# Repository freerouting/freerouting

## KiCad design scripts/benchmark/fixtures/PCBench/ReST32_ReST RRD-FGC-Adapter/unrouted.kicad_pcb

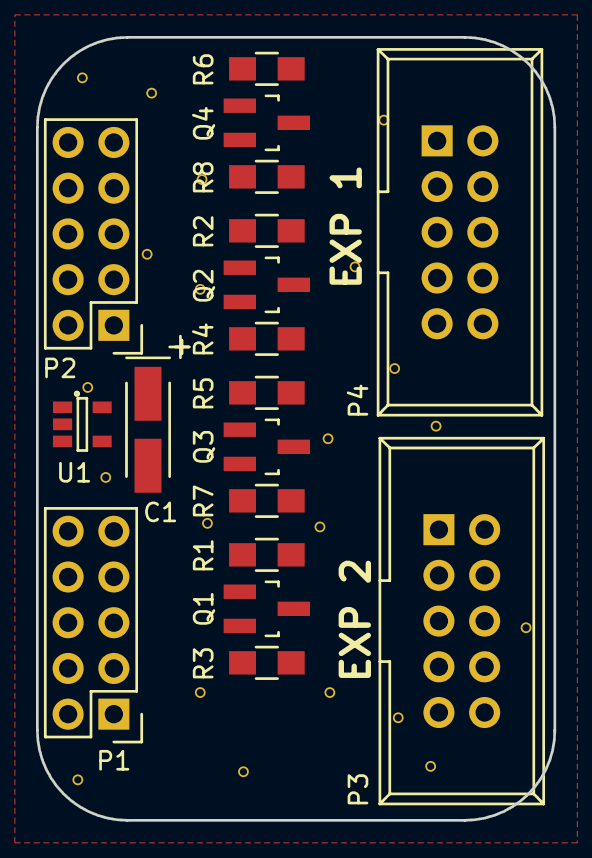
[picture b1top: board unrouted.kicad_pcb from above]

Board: 2 copper layers, 28.8 x 43.5 mm, 18 parts (0 on the bottom side), 23 nets, no tracks yet.

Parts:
C1: 2.2uF; TantalC_SizeA_EIA-3216_HandSoldering
P1, P2: CONN_02X05; Pin_Header_Straight_2x05
P3, P4: CONN_02X05; IDC_Header_Straight_10pins
Q1, Q2, Q3, Q4: BSS138; SOT-23_Handsoldering
R1, R2, R3, R4, R5, R6, R7, R8: 10K; R_0805_HandSoldering
U1: MIC5205; SOT-23-5

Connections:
+3V3: C1.1, Q1.3, Q2.3, Q3.3, Q4.3, R1.1, R2.1, R5.1, R6.1, U1.5
+5V: P2.2, P3.1, R3.1, R4.1, R7.1, R8.1, U1.1, U1.3
/BEEP: P3.10, Q1.2, R3.2
/CS: P4.7, Q2.2, R4.2
/DISPLAY_CD: P1.2, P3.8
/DISPLAY_CS: P1.1, P3.7
/DISPLAY_D0: P1.4, P3.5
/DISPLAY_D1: P1.3, P3.6
/DISPLAY_D2: P1.6, P3.3
/DISPLAY_D3: P1.5, P3.4
/DISPLAY_D4: P1.8, P4.6
/DISPLAY_D5: P1.7, P4.4
/DISPLAY_D6: P1.10, P3.9
/DISPLAY_D7: P1.9, P4.8
/DISPLAY_RD: P2.3, P4.3
/DISPLAY_WR: P2.4, Q1.1, R1.2
/MISO: P2.10, P4.10
/MOSI: P4.5, Q4.2, R8.2
/SCK: P4.9, Q3.2, R7.2
/SPI_CS1: P2.8, Q2.1, R2.2
/SPI_MOSI: P2.7, Q4.1, R6.2
/SPI_SCK: P2.9, Q3.1, R5.2
GND: C1.2, P2.1, P3.2, U1.2

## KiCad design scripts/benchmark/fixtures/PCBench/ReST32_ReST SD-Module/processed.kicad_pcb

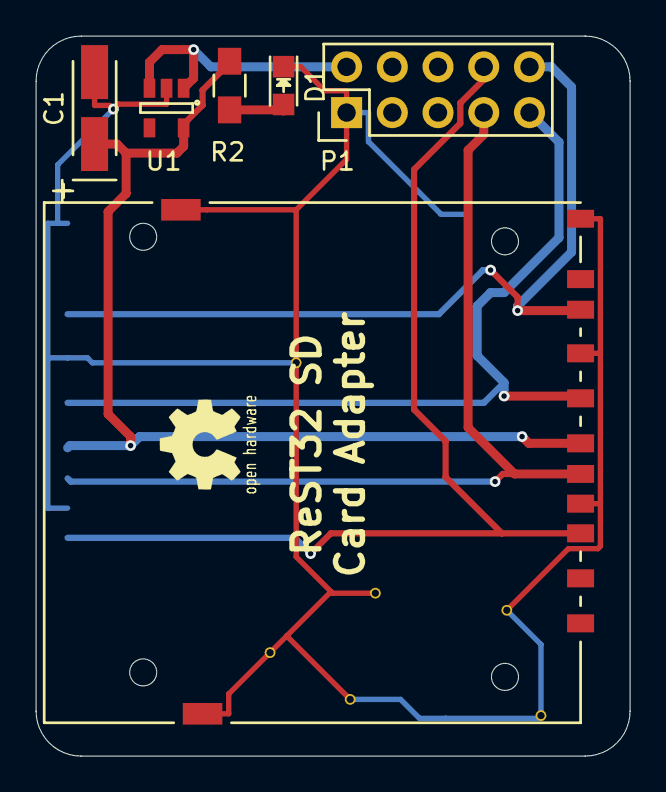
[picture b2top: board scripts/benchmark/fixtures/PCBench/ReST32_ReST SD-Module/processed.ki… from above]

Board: 2 copper layers, 33.0 x 40.0 mm, 7 parts (1 on the bottom side), 8 nets.

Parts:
C1: 2.2uF; TantalC_SizeA_EIA-3216_HandSoldering
CON1, CON2: uSD_Card; SD_Card_Receptacle
D1: Led_Small; LED_0805
P1: CONN_02X05; Pin_Header_Straight_2x05
R2: 1K; R_0805_HandSoldering
U1: MIC5205; SOT-23-5

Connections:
+3V3: C1.1, CON1.4, CON2.4, R2.1, U1.5
+5V: P1.2, U1.1, U1.3
/SPI-CS: CON1.2, CON2.2, P1.8
/SPI-MISO: CON1.7, CON2.7, P1.10
/SPI-MOSI: CON1.3, CON2.3, P1.7
/SPI-SCK: CON1.5, CON2.5, P1.9
GND: C1.2, CON1.6, CON1.10, CON1.11, CON1.12, CON1.13, CON2.6, CON2.10, CON2.11, CON2.12, CON2.13, D1.1, P1.1, U1.2
unnamed: D1.2, R2.2

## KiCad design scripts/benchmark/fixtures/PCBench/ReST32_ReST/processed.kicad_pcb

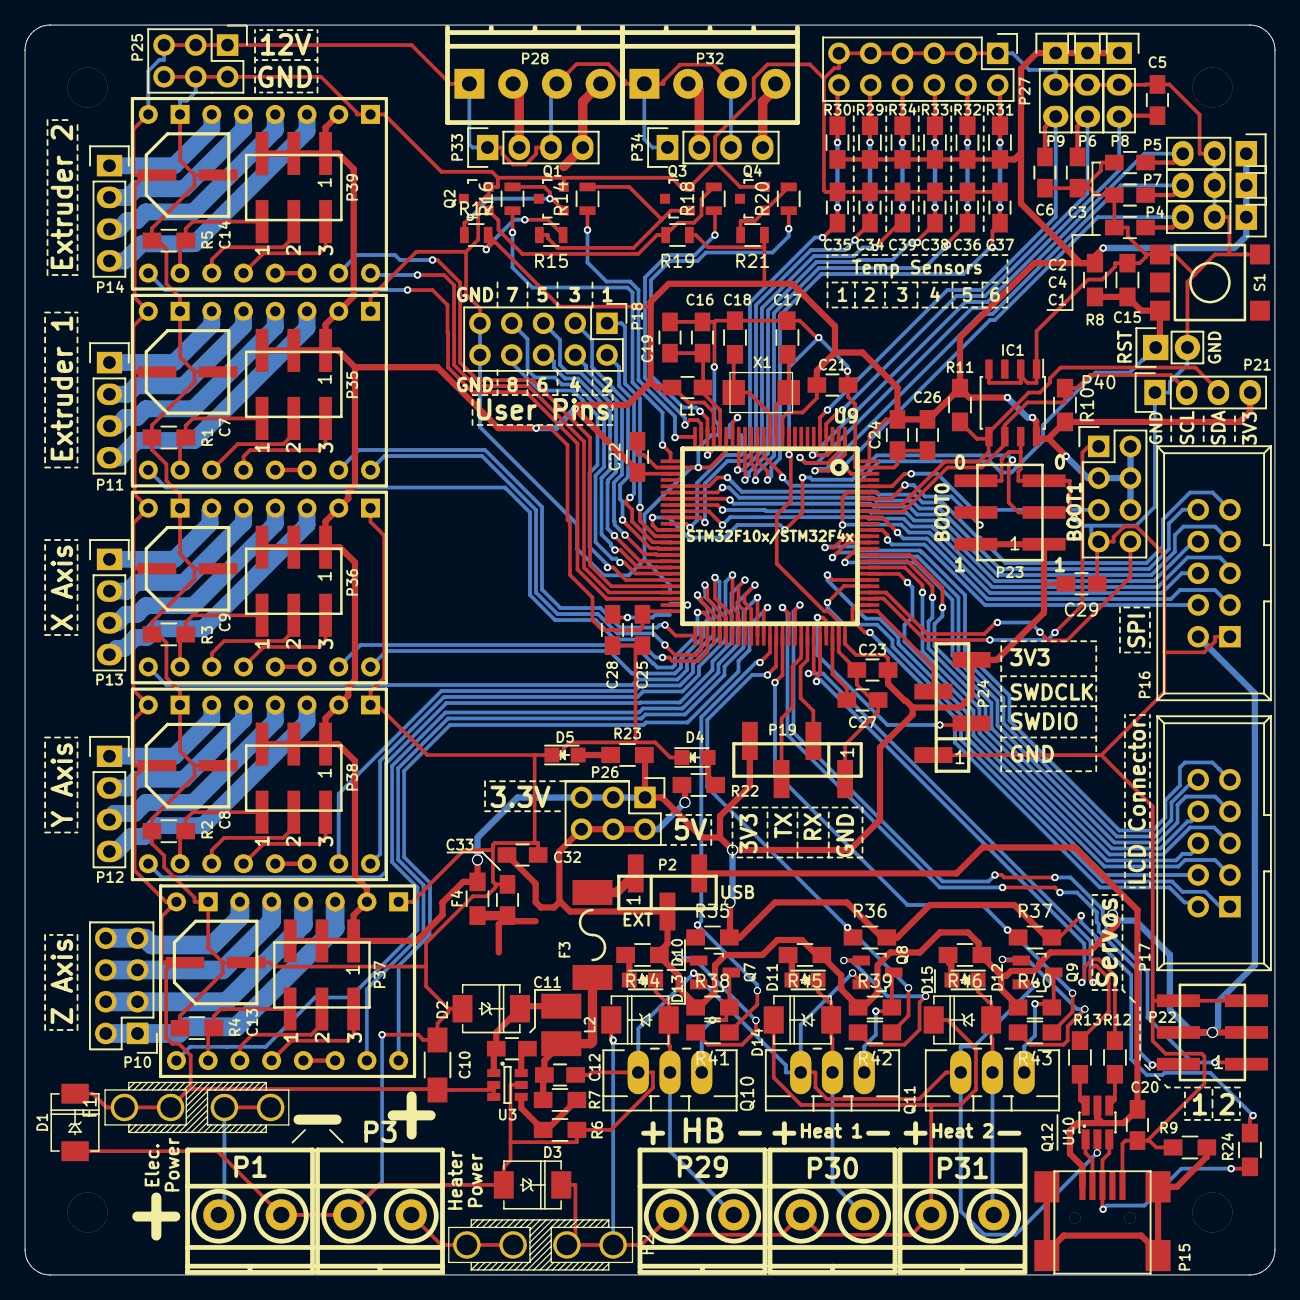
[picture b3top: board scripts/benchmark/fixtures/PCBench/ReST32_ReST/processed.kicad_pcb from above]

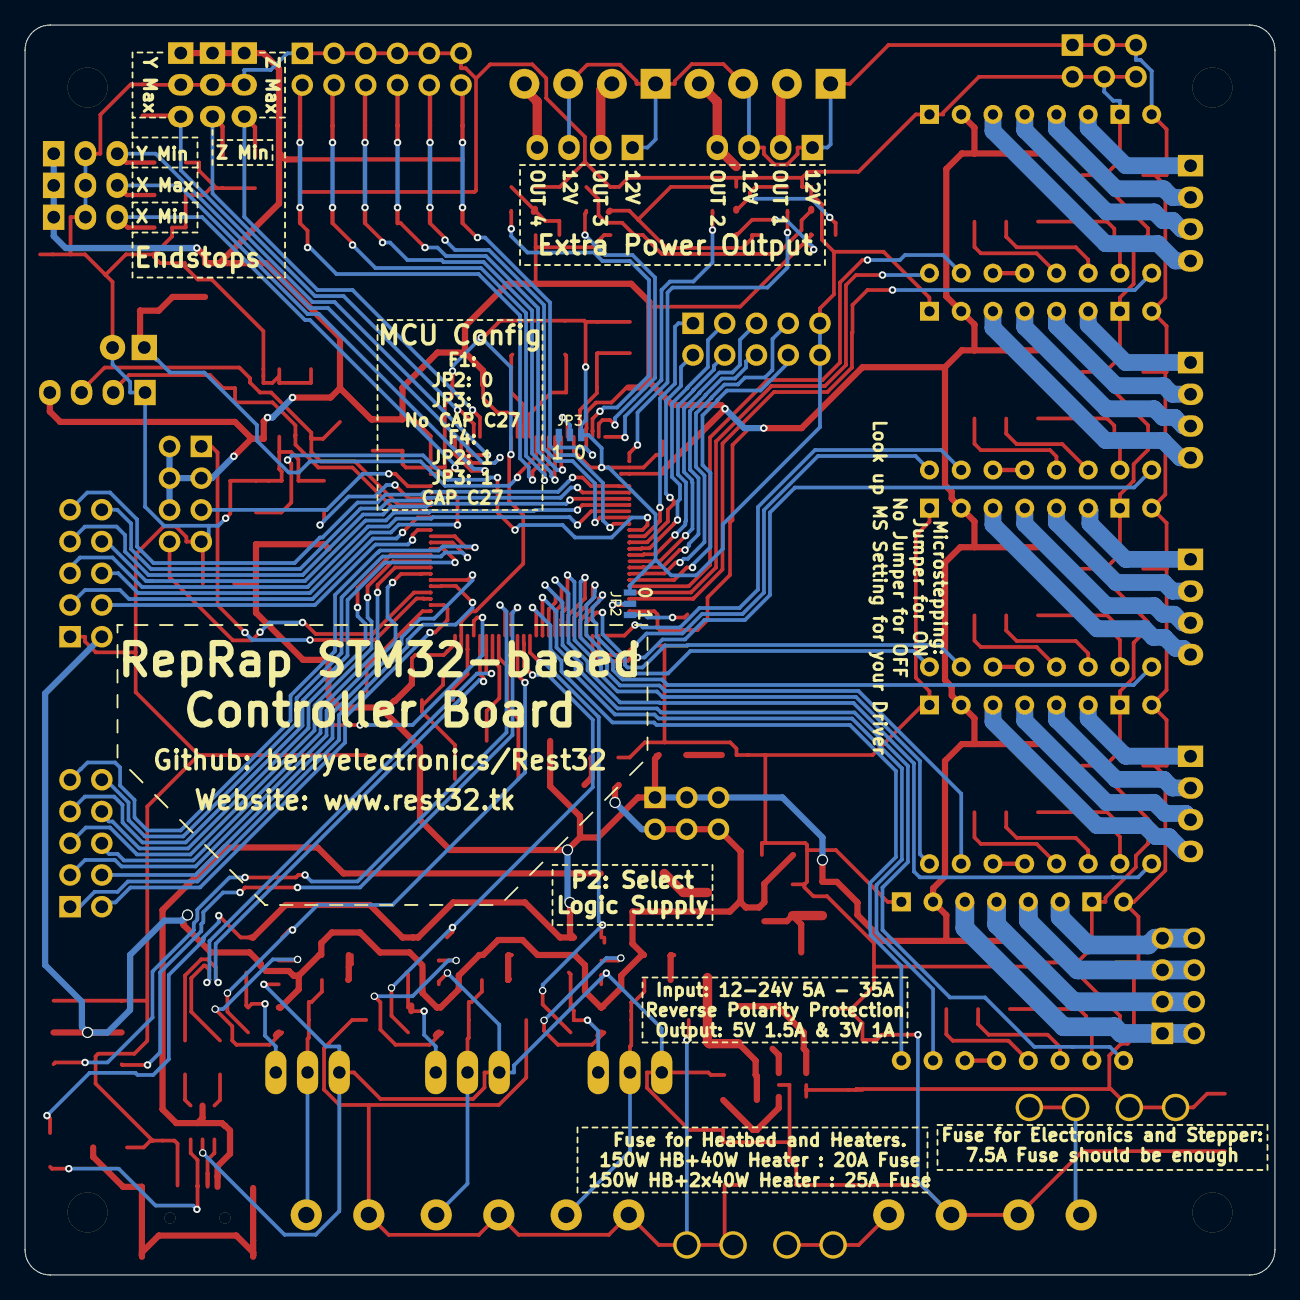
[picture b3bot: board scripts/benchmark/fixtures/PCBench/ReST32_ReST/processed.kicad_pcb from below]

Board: 2 copper layers, 100.0 x 100.0 mm, 159 parts (2 on the bottom side), 164 nets.

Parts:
C1, C2, C3, C4, C5, C6: 10nF; C_0805_HandSoldering
C7, C8, C9, C13, C14: 100uF; CP-PANASONIC-SMT_D8
C10: 10uF; C_1206_HandSoldering
C11: 22nF; C_0805_HandSoldering
C12, C26: 4.7uF; C_0805_HandSoldering
C15: 100nF; R_0805_HandSoldering
C16, C32, C33, C34, C35, C36, C37, C38, C39: 10uF; C_0805_HandSoldering
C17, C18: 10pF; R_0805_HandSoldering
C19, C20, C21, C22, C23, C24, C25, C29: 100nF; C_0805_HandSoldering
C27, C28: 2u2; C_0805_HandSoldering
D1, D3: 1N400x; DO-214AC.SMA
D2: B240A; DO-214AC.SMA
D4, D5, D10, D11, D12: LED; LED_0805
D13, D14, D15: D_1N400x-SMD; DO-214AC.SMA
F1, F2: F_Small; MINI-FUSE
F3: F_Small; FUSE-1812
F4: F_Small; R_0805_HandSoldering
IC1: AT24C256; SOIC-8_3.9x4.9mm_Pitch1.27mm
JP2, JP3: JUMPER3; S_JUMPER_3
L1: BEAD; C_0805_HandSoldering
L2: 4.7uH; CD32
P1, P3, P29, P30, P31: CONN_01X02; screw-5-2P
P2: CONN_01X03; bb02-hy03a
P4, P5, P6, P7, P8, P9: CONN_01X03; Pin_Header_Straight_1x03
P10, P40: CONN_02X04; Pin_Header_Straight_2x04
P11, P12, P13, P14, P21: CONN_01X04; Pin_Header_Straight_1x04
P15: USB_OTG; USB_Mini-B
P16, P17: CONN_02X05; IDC_Header_Straight_10pins
P18: CONN_02X05; Pin_Header_Straight_2x05
P19, P24: CONN_01X04; bb02-hy04a
P20: CONN_01X02; Pin_Header_Straight_1x02
P22, P23, P35, P36, P37, P38, P39: CONN_02X03; bb02-hp06
P25, P26: CONN_02X03; Pin_Header_Straight_2x03
P27: CONN_02X06; Pin_Header_Straight_2x06
P28, P32: CONN_02X02; pt_1,5-4-3,5-h
P33, P34: CONN_02X02; Pin_Header_Straight_1x04
Q1, Q2, Q3, Q4, Q7, Q8, Q9: BSS138; SOT-23
Q10, Q11, Q12: Q_AOT240L; TO-220_Neutral123_Vertical_LargePads
R1, R2, R3, R4, R5, R35, R36, R37, R38, R39, R40: 100K; R_0805_HandSoldering
R6: 28.7k; R_0805_HandSoldering
R7: 150K; R_0805_HandSoldering
R8: 10K; R_0805_HandSoldering
R9: 1M; R_0805_HandSoldering
R10, R11, R29, R30, R31, R32, R33, R34: 4K7; R_0805_HandSoldering
R12, R13, R41, R42, R43: 22R; R_0805_HandSoldering
R14, R16, R18, R20: 22R; R_0805
R15, R17, R19, R21: 100K; R_0805
R22, R23, R44, R45, R46: 1K; R_0805_HandSoldering
R24: 1K5; R_0805_HandSoldering
S1: SW_DIP_x2; SMD-BUTTON-6MM
U2, U5, U6, U7, U8: POLOLU_A4988; SWDIP8_.6W
U3: ACT4088; SOT-23-6
U9: STM32F10x/STM32F4x; LQFP100-14x14
U10: USBLC6-2; SOT32-6L
X1: Crystal_Small; 2P-5032

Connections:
+3V3: C21.1, C22.1, C23.1, C24.1, C25.1, C26.1, C29.2, F4.1, IC1.8, JP3.1, L1.1, P4.1, P5.1, P6.1, P7.1, P8.1, P9.1, P19.4, P21.4, P23.1, P23.2, P24.4, P26.1, P26.3, P26.5, P35.1, P35.3, P35.5, P36.1, P36.3, P36.5, P37.1, P37.3, P37.5, P38.1, P38.3, P38.5, P39.1, P39.3, P39.5, P40.2, P40.3, P40.4, P40.6, R8.2, R10.2, R11.2, R15.1, R17.2, R19.1, R21.1, R23.1, R24.2, R29.2, R30.2, R31.2, R32.2, R33.2, R34.2, R35.2, R36.2, R37.2, U2.2, U5.2, U6.2, U7.2, U8.2, U9.11, U9.22, U9.28, U9.50, U9.75, U9.100
+5V: C32.2, P2.2, P16.2, P22.3, P22.4, P26.2, P26.4, P26.6, R22.1, R38.1, R39.1, R40.1, R44.1, R45.1, R46.1
+12V: C7.1, C8.1, C9.1, C10.1, C13.1, C14.1, D1.1, F1.2, P25.1, P25.3, P25.5, P28.1, P28.3, P32.1, P32.3, P33.1, P33.3, P34.1, P34.3, U2.8, U3.2, U3.3, U5.8, U6.8, U7.8, U8.8
+12VA: D3.1, D13.1, D14.1, D15.1, F2.2, P29.1, P30.1, P31.1
/Extra Power Output/EXTRA_0_OUT: P28.2, P33.2
/Extra Power Output/EXTRA_1_OUT: P28.4, P33.4
/Extra Power Output/EXTRA_2_OUT: P32.2, P34.2
/Extra Power Output/EXTRA_3_OUT: P32.4, P34.4
/Heater/H0_GATE: Q7.1, R41.2
/Heater/H1_GATE: Q8.1, R42.2
/Heater/H2_GATE: Q9.1, R43.2
/Heater/HEATER_0_5VL: Q7.3, Q10.1, R38.2
/Heater/HEATER_0_OUT: D10.1, D13.2, P29.2, Q10.2
/Heater/HEATER_1_5VL: Q8.3, Q11.1, R39.2
/Heater/HEATER_1_OUT: D11.1, D14.2, P30.2, Q11.2
/Heater/HEATER_2_5VL: Q9.3, Q12.1, R40.2
/Heater/HEATER_2_OUT: D12.1, D15.2, P31.2, Q12.2
/Logic/USBP_D+: P15.3, R24.1, U10.3
/Logic/USBP_D-: P15.2, U10.1
/Logic/USBR+: R12.1, U10.4
/Logic/USBR-: R13.2, U10.6
/Power Input/12V-R: F1.1, P1.1
/Power Input/12VA-R: F2.1, P3.2
/Stepper and Endstop/E0M1: P35.6, R1.1, U2.10
/Stepper and Endstop/E0M2: P35.4, U2.11
/Stepper and Endstop/E0M3: P35.2, U2.12
/Stepper and Endstop/E0_1A: P11.3, U2.4
/Stepper and Endstop/E0_1B: P11.4, U2.3
/Stepper and Endstop/E0_2A: P11.2, U2.5
/Stepper and Endstop/E0_2B: P11.1, U2.6
/Stepper and Endstop/E1M1: P39.6, R5.1, U8.10
/Stepper and Endstop/E1M2: P39.4, U8.11
/Stepper and Endstop/E1M3: P39.2, U8.12
/Stepper and Endstop/E1_1A: P14.3, U8.4
/Stepper and Endstop/E1_1B: P14.4, U8.3
/Stepper and Endstop/E1_2A: P14.2, U8.5
/Stepper and Endstop/E1_2B: P14.1, U8.6
/Stepper and Endstop/XM1: P36.6, R3.1, U6.10
/Stepper and Endstop/XM2: P36.4, U6.11
/Stepper and Endstop/XM3: P36.2, U6.12
/Stepper and Endstop/X_1A: P13.3, U6.4
/Stepper and Endstop/X_1B: P13.4, U6.3
/Stepper and Endstop/X_2A: P13.2, U6.5
/Stepper and Endstop/X_2B: P13.1, U6.6
/Stepper and Endstop/YM1: P38.6, R2.1, U5.10
/Stepper and Endstop/YM2: P38.4, U5.11
/Stepper and Endstop/YM3: P38.2, U5.12
/Stepper and Endstop/Y_1A: P12.3, U5.4
/Stepper and Endstop/Y_1B: P12.4, U5.3
/Stepper and Endstop/Y_2A: P12.2, U5.5
/Stepper and Endstop/Y_2B: P12.1, U5.6
/Stepper and Endstop/ZM1: P37.6, R4.1, U7.10
/Stepper and Endstop/ZM2: P37.4, U7.11
/Stepper and Endstop/ZM3: P37.2, U7.12
/Stepper and Endstop/Z_1A: P10.3, P10.4, U7.4
/Stepper and Endstop/Z_1B: P10.1, P10.2, U7.3
/Stepper and Endstop/Z_2A: P10.5, P10.6, U7.5
/Stepper and Endstop/Z_2B: P10.7, P10.8, U7.6
BOOT_0: P23.4, U9.94
BOOT_1: P23.3, U9.37
DISPLAY_CD: P17.2, U9.77
DISPLAY_CS: P17.1, U9.80
DISPLAY_D0: P17.4, U9.81
DISPLAY_D1: P17.3, U9.82
DISPLAY_D2: P17.6, U9.83
DISPLAY_D3: P17.5, U9.84
DISPLAY_D4: P17.8, U9.85
DISPLAY_D5: P17.7, U9.86
DISPLAY_D6: P17.10, U9.87
DISPLAY_D7: P17.9, U9.88
DISPLAY_EXTRA_0: P16.6, U9.95
DISPLAY_EXTRA_1: P40.5, U9.96
DISPLAY_RD: P16.3, U9.91
DISPLAY_WR: P16.4, U9.89
ENDSTOP_X_MAX: C4.1, P7.3, U9.1
ENDSTOP_X_MIN: C1.1, P4.3, U9.98
ENDSTOP_Y_MAX: C5.1, P8.3, U9.3
ENDSTOP_Y_MIN: C2.1, P5.3, U9.2
ENDSTOP_Z_MAX: C6.1, P9.3, U9.5
ENDSTOP_Z_MIN: C3.1, P6.3, U9.4
EXTRA_0: R16.1, U9.26
EXTRA_1: R14.1, U9.25
EXTRA_2: R18.1, U9.24
EXTRA_3: R20.1, U9.23
GND: C1.2, C2.2, C3.2, C4.2, C5.2, C6.2, C7.2, C8.2, C9.2, C10.2, C12.2, C13.2, C14.2, C15.1, C16.2, C17.1, C18.2, C19.2, C20.2, C21.2, C22.2, C23.2, C24.2, C25.2, C26.2, C27.2, C28.2, C29.1, C32.1, C33.2, C34.2, C35.2, C36.2, C37.2, C38.2, C39.2, D1.2, D2.2, D3.2, D4.1, D5.1, IC1.1, IC1.2, IC1.4, IC1.7, JP2.3, JP3.3, P1.2, P3.1, P4.2, P5.2, P6.2, P7.2, P8.2, P9.2, P15.5, P16.1, P18.9, P18.10, P19.1, P20.2, P21.1, P22.5, P22.6, P23.5, P23.6, P24.1, P25.2, P25.4, P25.6, P27.1, P27.3, P27.5, P27.7, P27.9, P27.11, P40.7, Q1.2, Q2.2, Q3.2, Q4.2, Q7.2, Q8.2, Q9.2, Q10.3, Q11.3, Q12.3, R1.2, R2.2, R3.2, R4.2, R5.2, R6.1, R9.1, S1.3, S1.4, U2.1, U2.7, U3.5, U5.1, U5.7, U6.1, U6.7, U7.1, U7.7, U8.1, U8.7, U9.10, U9.20, U9.27, U9.74, U9.99, U10.2
HEATER_0: R35.1, R41.1, U9.63
HEATER_1: R36.1, R42.1, U9.64
HEATER_2: R37.1, R43.1, U9.65
I2C_SCL: IC1.6, P21.2, R10.1, U9.92
I2C_SDA: IC1.5, P21.3, R11.1, U9.93
unnamed: C11.1, D2.1, L2.1, U3.1
unnamed: C11.2, U3.6
unnamed: C12.1, F3.2, L2.2, R7.2
unnamed: C16.1, C19.1, L1.2, U9.21
unnamed: C17.2, U9.12, X1.2
unnamed: C18.1, U9.13, X1.1
unnamed: C28.1, JP2.1
unnamed: C33.1, F4.2
unnamed: D4.2, R22.2
unnamed: D5.2, R23.2
unnamed: D10.2, R44.2
unnamed: D11.2, R45.2
unnamed: D12.2, R46.2
unnamed: P15.6, R9.2
unnamed: Q1.1, R16.2, R17.1
unnamed: Q2.1, R18.2, R19.2
unnamed: Q3.1, R14.2, R15.2
unnamed: Q4.1, R20.2, R21.2
unnamed: R6.2, R7.1, U3.4
unnamed: U2.13, U2.14
unnamed: U5.13, U5.14
unnamed: U6.13, U6.14
unnamed: U7.13, U7.14
unnamed: U8.13, U8.14
P_VCAP_1: JP2.2, U9.49
P_VCAP_2: C27.1, U9.73
P_VSSA: JP3.2, U9.19
RESET: C15.2, P20.1, R8.1, S1.2, U9.14
SERVO_0: P22.2, U9.66
SERVO_1: P22.1, U9.67
SPI_CS1: P16.8, U9.33
SPI_CS2: P16.5, U9.34
SPI_MISO: P16.10, U9.31
SPI_MOSI: P16.7, U9.32
SPI_SCK: P16.9, U9.30
STEPPER_E_0_DIR: U2.16, U9.52
STEPPER_E_0_EN: U2.9, U9.53
STEPPER_E_0_STEP: U2.15, U9.51
STEPPER_E_1_DIR: U8.16, U9.47
STEPPER_E_1_EN: U8.9, U9.48
STEPPER_E_1_STEP: U8.15, U9.46
STEPPER_X_DIR: U6.16, U9.55
STEPPER_X_EN: U6.9, U9.56
STEPPER_X_STEP: U6.15, U9.54
STEPPER_Y_DIR: U5.16, U9.58
STEPPER_Y_EN: U5.9, U9.59
STEPPER_Y_STEP: U5.15, U9.57
STEPPER_Z_DIR: U7.16, U9.62
STEPPER_Z_EN: U7.9, U9.60
STEPPER_Z_STEP: U7.15, U9.61
SWD_CLK: P24.3, U9.76
SWD_IO: P24.2, U9.72
TEMP_0: C37.1, P27.2, R31.1, U9.15
TEMP_1: C36.1, P27.4, R32.1, U9.16
TEMP_2: C38.1, P27.6, R33.1, U9.17
TEMP_3: C39.1, P27.8, R34.1, U9.18
TEMP_4: C34.1, P27.10, R29.1, U9.35
TEMP_5: C35.1, P27.12, R30.1, U9.36
UART_1_RX: P19.2, U9.69
UART_1_TX: P19.3, U9.68
UART_4_RX: P40.8, U9.79
UART_4_TX: P40.1, U9.78
USB_MCU+: R12.2, U9.71
USB_MCU-: R13.1, U9.70
USER_0: P18.1, U9.38
USER_1: P18.2, U9.39
USER_2: P18.3, U9.40
USER_3: P18.4, U9.41
USER_4: P18.5, U9.42
USER_5: P18.6, U9.43
USER_6: P18.7, U9.44
USER_7: P18.8, U9.45
VCC: C20.1, P2.3, P15.1, U10.5
VEE: F3.1, P2.1

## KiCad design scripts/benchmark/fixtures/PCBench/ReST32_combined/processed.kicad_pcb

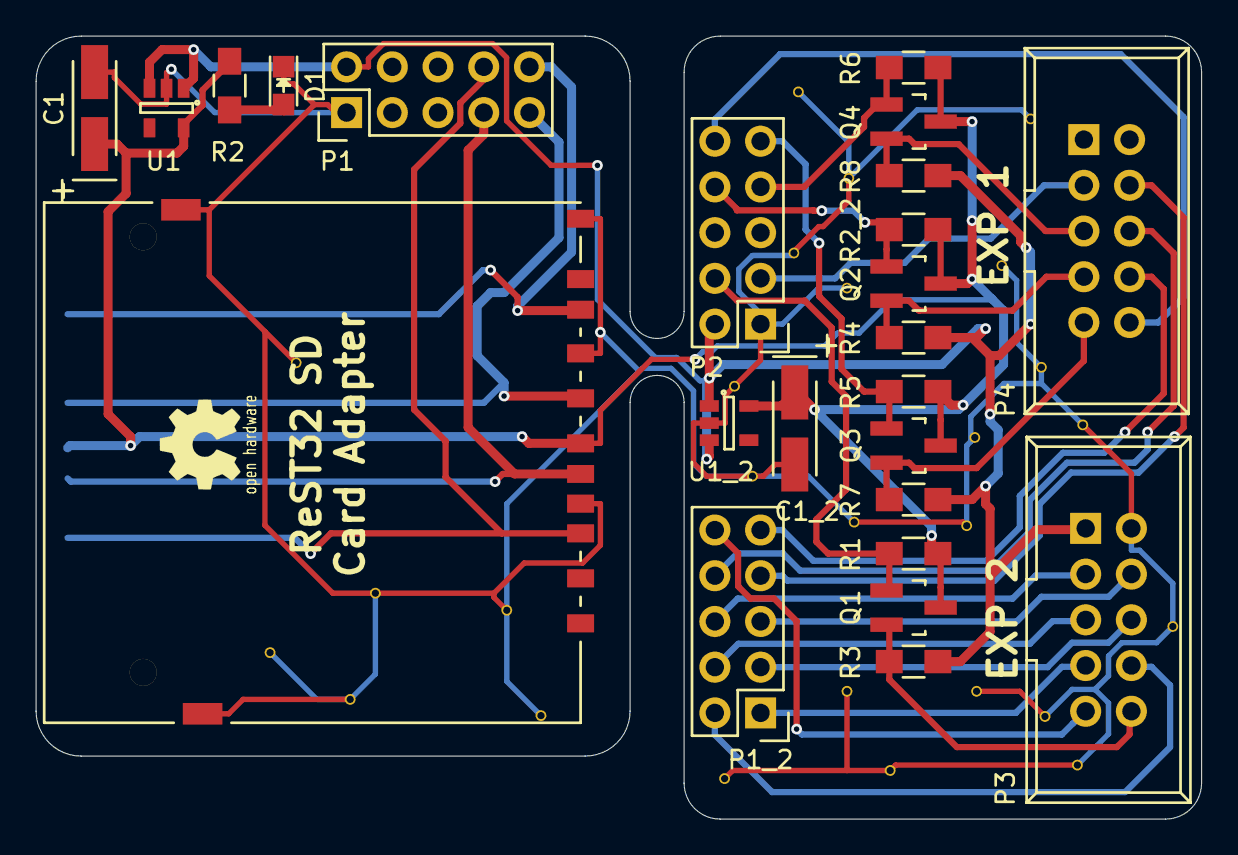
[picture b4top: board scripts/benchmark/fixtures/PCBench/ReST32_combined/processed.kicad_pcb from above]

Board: 2 copper layers, 64.8 x 43.5 mm, 24 parts (0 on the bottom side), 28 nets.

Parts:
C1: CP1_Small; TantalC_SizeA_EIA-3216_HandSoldering
C1_2: 2.2uF; TantalC_SizeA_EIA-3216_HandSoldering
CON1: uSD_Card; SD_Card_Receptacle
D1: Led_Small; LED_0805
P1, P1_2, P2: CONN_02X05; Pin_Header_Straight_2x05
P3, P4: CONN_02X05; IDC_Header_Straight_10pins
Q1, Q2, Q3, Q4: BSS138; SOT-23_Handsoldering
R1, R2_2, R3, R4, R5, R6, R7, R8: 10K; R_0805_HandSoldering
R2: 1K; R_0805_HandSoldering
U1, U1_2: MIC5205; SOT-23-5

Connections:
+3V3: C1.1, C1_2.1, CON1.4, Q1.3, Q2.3, Q3.3, Q4.3, R1.1, R2.1, R2_2.1, R5.1, R6.1, U1.5, U1_2.5
+5V: P1.2, P2.2, P3.1, R3.1, R4.1, R7.1, R8.1, U1.1, U1.3, U1_2.1, U1_2.3
/BEEP: P3.10, Q1.2, R3.2
/CS: P4.7, Q2.2, R4.2
/DISPLAY_CD: P1_2.2, P3.8
/DISPLAY_CS: P1_2.1, P3.7
/DISPLAY_D0: P1_2.4, P3.5
/DISPLAY_D1: P1_2.3, P3.6
/DISPLAY_D2: P1_2.6, P3.3
/DISPLAY_D3: P1_2.5, P3.4
/DISPLAY_D4: P1_2.8, P4.6
/DISPLAY_D5: P1_2.7, P4.4
/DISPLAY_D6: P1_2.10, P3.9
/DISPLAY_D7: P1_2.9, P4.8
/DISPLAY_RD: P2.3, P4.3
/DISPLAY_WR: P2.4, Q1.1, R1.2
/MISO: P2.10, P4.10
/MOSI: P4.5, Q4.2, R8.2
/SCK: P4.9, Q3.2, R7.2
/SPI-CS: CON1.2, P1.8
/SPI-MISO: CON1.7, P1.10
/SPI-MOSI: CON1.3, P1.7
/SPI-SCK: CON1.5, P1.9
/SPI_CS1: P2.8, Q2.1, R2_2.2
/SPI_MOSI: P2.7, Q4.1, R6.2
/SPI_SCK: P2.9, Q3.1, R5.2
GND: C1.2, C1_2.2, CON1.6, CON1.10, CON1.11, CON1.12, CON1.13, D1.1, P1.1, P2.1, P3.2, U1.2, U1_2.2
unnamed: D1.2, R2.2
